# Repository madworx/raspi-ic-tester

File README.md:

# ic-tester

Minimalistic tester for integrated circuits, using Raspberry PI.

## Status

First copy has been build, tested and is working.

Software draft has been written and is working, files in `software/` subdirectory. Run the `raspi-ic-tester.py` script. IC definitions are in `*.md` files.

Case was printed, but tolerances were too low.

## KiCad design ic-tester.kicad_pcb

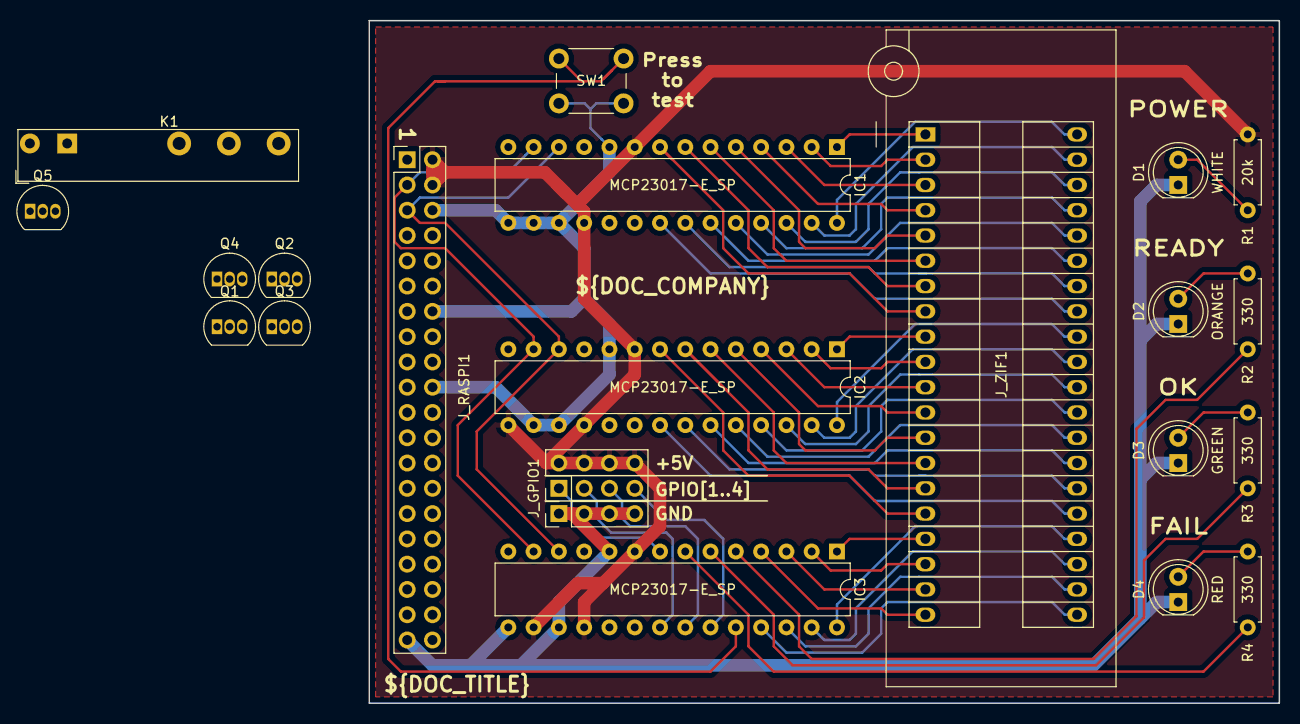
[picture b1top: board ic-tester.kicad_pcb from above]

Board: 2 copper layers, 91.4 x 68.6 mm, 22 parts (0 on the bottom side), 61 nets.

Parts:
D1: WHITE; LED_D5.0mm_Clear
D2: ORANGE; LED_D5.0mm
D3: GREEN; LED_D5.0mm
D4: RED; LED_D5.0mm
IC1, IC2, IC3: MCP23017-E_SP; DIP-28_W7.62mm
J1: Conn_01x04; PinHeader_1x04_P2.54mm_Vertical
J_GPIO1: Conn_02x04_Odd_Even; PinHeader_2x04_P2.54mm_Vertical
J_RASPI1: Raspberry_Pi_2_3; PinHeader_2x20_P2.54mm_Vertical
J_ZIF1: Conn_02x20_Counter_Clockwise; 3M_Textool_240-1288-00-0602J_2x20_P2.54mm
K1: FINDER-34.51; Relay_SPDT_Finder_34.51_Vertical
Q1, Q2: BC547; TO-92_Inline
Q3, Q4, Q5: BS250; TO-92_Inline
R1: 20k; R_Axial_DIN0207_L6.3mm_D2.5mm_P7.62mm_Horizontal
R2, R3, R4: 330; R_Axial_DIN0207_L6.3mm_D2.5mm_P7.62mm_Horizontal
SW1: SW_SPST; SW_PUSH_6mm_H13mm

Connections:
/GPIO1: IC3.8, J_GPIO1.1
/GPIO2: IC3.21, J_GPIO1.3
/GPIO3: IC3.22, J_GPIO1.5
/GPIO4: IC3.23, J_GPIO1.7
/I2C-EXP-GPIO: K1.12, Q5.2
/LED_FAIL: IC3.7, R4.2
/LED_OK: IC3.6, R3.2
/LED_RDY: IC3.5, R2.2
/MAIN_VDD: Q3.3, Q4.3
/SCL: IC1.12, IC2.12, IC3.12, J_RASPI1.5
/SDA: IC1.13, IC2.13, IC3.13, J_RASPI1.3
/SW_TEST: IC3.24, SW1.1
/ZIF01: IC1.1, J_ZIF1.1
/ZIF02: IC1.2, J_ZIF1.2
/ZIF03: IC1.3, J_ZIF1.3
/ZIF04: IC1.4, J_ZIF1.4
/ZIF05: IC1.5, J_ZIF1.5
/ZIF06: IC1.6, J_ZIF1.6
/ZIF07: IC1.7, J_ZIF1.7
/ZIF08: IC1.8, J_ZIF1.8
/ZIF09: IC2.1, J_ZIF1.9
/ZIF10: IC2.2, J_ZIF1.10
/ZIF11: IC2.3, J_ZIF1.11
/ZIF12: IC2.4, J_ZIF1.12
/ZIF13: IC2.5, J_ZIF1.13
/ZIF14: IC2.6, J_ZIF1.14
/ZIF15: IC2.7, J_ZIF1.15
/ZIF16: IC2.8, J_ZIF1.16
/ZIF17: IC3.1, J_ZIF1.17
/ZIF18: IC3.2, J_ZIF1.18
/ZIF19: IC3.3, J_ZIF1.19
/ZIF20: IC3.4, J_ZIF1.20
/ZIF21: IC3.25, J_ZIF1.21
/ZIF22: IC3.26, J_ZIF1.22
/ZIF23: IC3.27, J_ZIF1.23
/ZIF24: IC3.28, J_ZIF1.24
/ZIF25: IC2.21, J_ZIF1.25
/ZIF26: IC2.22, J_ZIF1.26
/ZIF27: IC2.23, J_ZIF1.27
/ZIF28: IC2.24, J_ZIF1.28
/ZIF29: IC2.25, J_ZIF1.29
/ZIF30: IC2.26, J_ZIF1.30
/ZIF31: IC2.27, J_ZIF1.31
/ZIF32: IC2.28, J_ZIF1.32
/ZIF33: IC1.21, J_ZIF1.33
/ZIF34: IC1.22, J_ZIF1.34
/ZIF35: IC1.23, J_ZIF1.35
/ZIF36: IC1.24, J_ZIF1.36
/ZIF37: IC1.25, J_ZIF1.37
/ZIF38: IC1.26, J_ZIF1.38
/ZIF39: IC1.27, J_ZIF1.39
/ZIF40: IC1.28, J_ZIF1.40
GND: D1.1, D2.1, D3.1, D4.1, IC1.10, IC1.15, IC1.16, IC1.17, IC2.10, IC2.16, IC2.17, IC3.10, IC3.15, IC3.17, J1.1, J1.2, J1.3, J1.4, J_RASPI1.6, J_RASPI1.9, J_RASPI1.14, J_RASPI1.20, J_RASPI1.25, J_RASPI1.30, J_RASPI1.34, J_RASPI1.39, K1.A2, Q1.3, Q2.3, SW1.2
unnamed: D1.2, R1.1
unnamed: D2.2, R2.1
unnamed: D3.2, R3.1
unnamed: D4.2, R4.1
unnamed: K1.14, Q5.3
unnamed: Q1.1, Q2.2, Q4.2
unnamed: Q2.1, Q3.2
VDD: IC1.9, IC1.18, IC2.9, IC2.15, IC2.18, IC3.9, IC3.16, IC3.18, J_GPIO1.2, J_GPIO1.4, J_GPIO1.6, J_GPIO1.8, J_RASPI1.2, J_RASPI1.4, Q3.1, R1.2

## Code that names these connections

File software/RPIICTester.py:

# pylint: disable=invalid-name
"""Raspberry PI IC Tester.
Repository: https://github.com/madworx/raspi-ic-tester
"""

import csv
import re
import time

import adafruit_mcp230xx
import board
import busio
import digitalio

class RPIICTester(object):
    """Main class for the Raspiberry PI IC Tester.
    Relies on the 'expander-netlist.csv' file to figure out which
    pins are connected to which pads.
    """
    def __init__(self):
        self._i2c = busio.I2C(board.SCL, board.SDA)
        self._mcps = {}
        self._pins = {}
        self._pindir = {}
        self._load_expander_netlist()

    def _load_expander_netlist(self):
        with open('expander-netlist.csv', 'r') as csvfile:
            mapreader = csv.reader(csvfile, delimiter=';')
            for row in mapreader:
                if len(row) == 3:
                    if row[0] not in self._mcps:
                        self._mcps[row[0]] = adafruit_mcp230xx.MCP23017(
                            self._i2c, address=int(row[0], base=16))
                    self._pins[row[2]] = self._mcps[row[0]].get_pin(
                        self._decode_padname_to_pin(row[1]))
                elif len(row) == 1 and row[0][0] == '#':
                    pass
                else:
                    raise AssertionError("Unable to parse row from netlist file.")

    @staticmethod
    def _decode_padname_to_pin(padname):
        matches = re.match(r'^GP([AB])([0-9])$', padname)
        if matches:
            return (ord(matches.group(1))-65)*8 + int(matches.group(2))
        else:
            raise AssertionError("Could not grok padname [{0}]".format(padname))

    def _get_pin(self, name):
        return self._pins[name]

    def _set_pin_direction(self,pin,direction):
        if pin in self._pindir:
            old_value = self._pindir[pin]
            if old_value == direction:
                return
        if direction == digitalio.Direction.INPUT:
            pin.direction = digitalio.Direction.INPUT
            pin.pull = None
        elif direction == digitalio.Direction.OUTPUT:
            pin.direction = digitalio.Direction.OUTPUT
        self._pindir[pin] = direction

    def zero_all_pins(self):
        """Put all pins into input mode with no pull-up."""
        for pinname in self._pins:
            pin = self._get_pin(pinname)
            self._set_pin_direction(pin,digitalio.Direction.INPUT)

    def read_pin(self, name):
        """Configure the given pin (e.g. "ZIF03") as an input pin,
        and read the value from it."""
        pin = self._get_pin(name)
        self._set_pin_direction(pin,digitalio.Direction.INPUT)
        return pin.value

    def set_pin(self, name, value=True):
        """Configure the given pin (e.g. "ZIF24") as an output pin,
        and set it to the specified value."""
        pin = self._get_pin(name)
        self._set_pin_direction(pin,digitalio.Direction.OUTPUT)
        pin.value = value

    def set_led_ok(self, value=True):
        """Set the "OK" LED"""
        self.set_pin('LED_OK', value)

    def set_led_fail(self, value=True):
        """Set the "FAIL" LED"""
        self.set_pin('LED_FAIL', value)

    def set_led_ready(self, value=True):
        """Set the "READY" LED"""
        self.set_pin('LED_RDY', value)

    def wait_for_press(self):
        """Wait until the "Press to test" button has been pressed"""
        self._get_pin('SW_TEST').pull = digitalio.Pull.UP
        while self.read_pin('SW_TEST'):
            time.sleep(0.05)

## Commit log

2019-01-02 Initial import.
2019-01-09 For production.
2019-01-10 Added 3D models for correctly coloured LEDs, as well as ZIF-socket. Reduced reundandant tracks.
2019-01-12 Completed PCB case in FreeCAD. Added draft for software part.
2019-02-01 Draft of software for the tester.
2019-02-01 Add code to have no pins set when exiting. Cleanup obsolete files.
2019-02-01 Integrate IC selector into one util.
2019-02-02 Broke out functionality into separate files/classes. Fixed linting.
2019-02-09 Minor changes to the software.
2019-02-09 Draft of version 2.0
2019-02-12 Updated README + Added photo of first product.
2019-02-16 Added test for 74HCT?273 (Octal D-type flip-flop with reset) - shout out to @tnn2 for the chip! All user to specify number of iterations to run.
2019-02-26 Added 74HC688 testing template.
2019-02-26 Software fixes * Don't set pin direction in hardware unless we need to. * Implement support for externally driven VDD/GND. (In addition i 1/0) * Make "x" actually work for output pins.
2019-02-26 IC definitions: Fixed 74(LS|HC)193 tests.
2019-02-26 74HC193: Added testing of carry/borrow pins.
2019-02-26 74HC74: Fixed definition. (~2CLR, not 2CLR).
2019-02-26 Implemented support for randomized input, as well as referencing a previously set input, to effecively clone that value. Implemented READY blinkenlights while testing is being performed.
2019-02-26 Adapted to use randomized inputs for the testing.
